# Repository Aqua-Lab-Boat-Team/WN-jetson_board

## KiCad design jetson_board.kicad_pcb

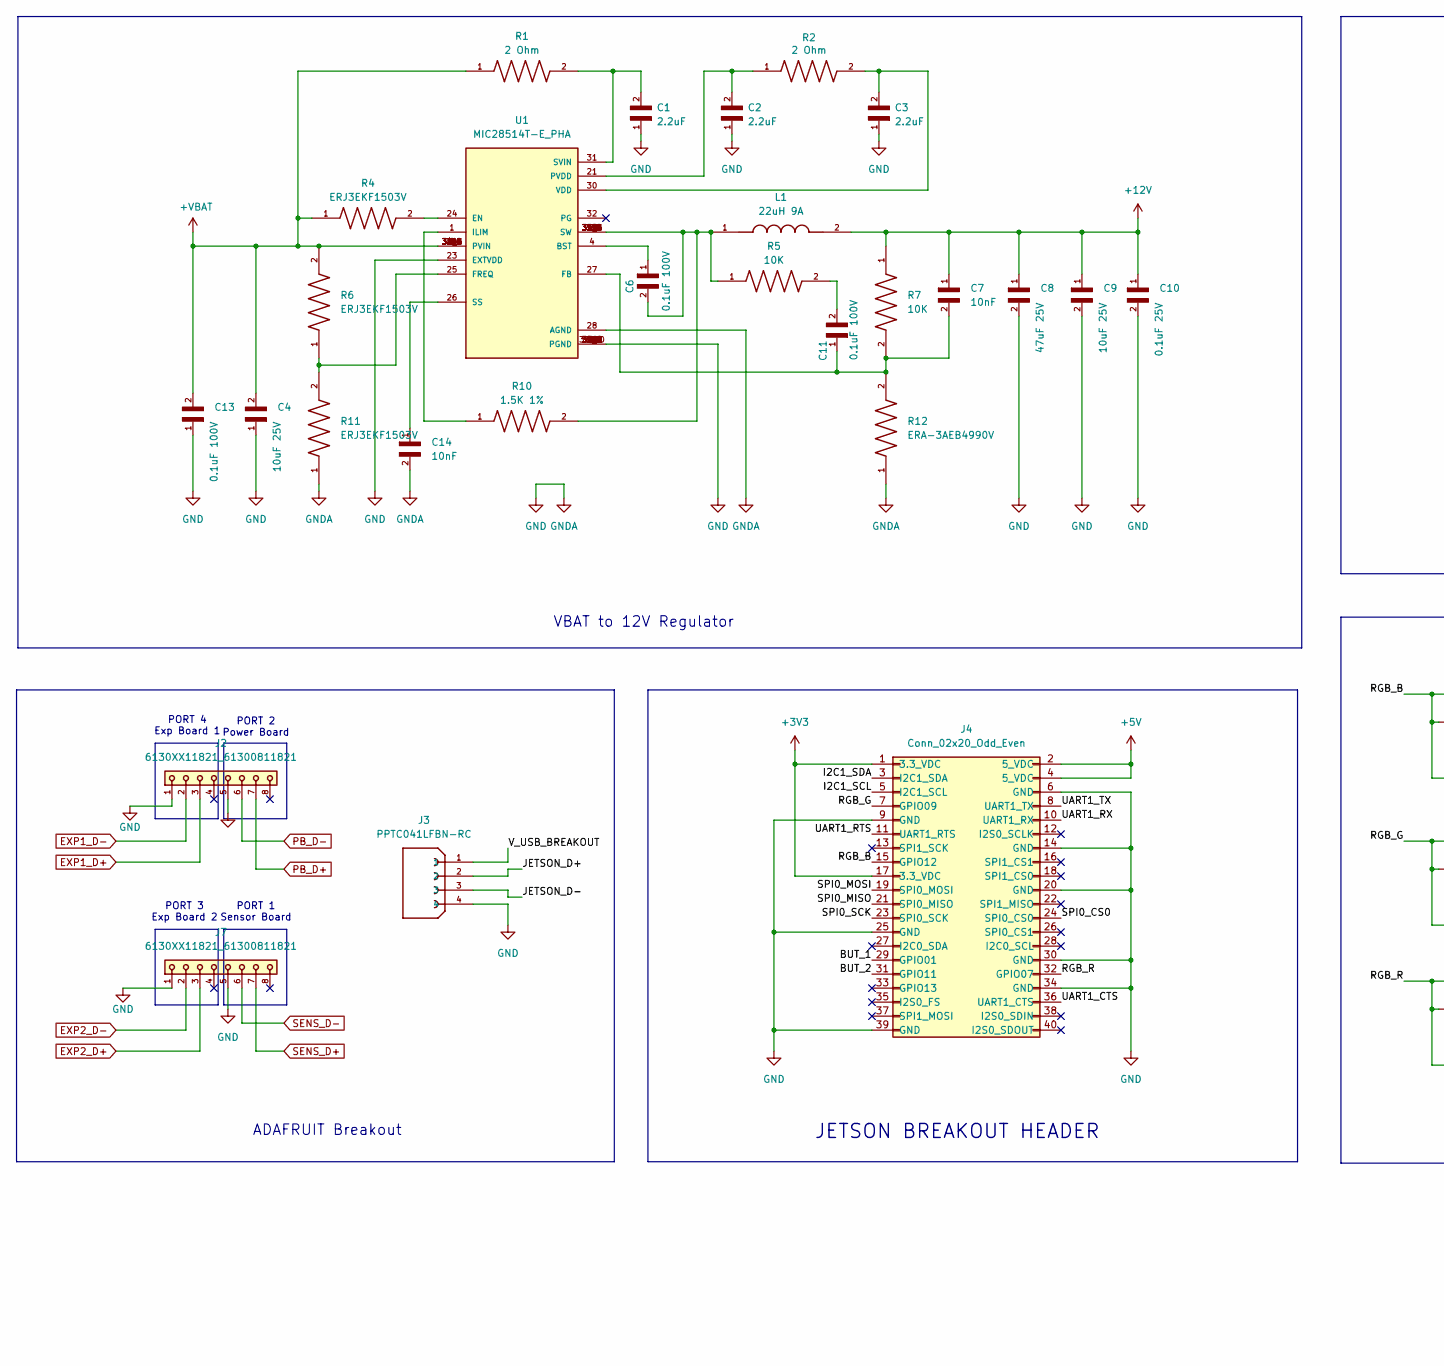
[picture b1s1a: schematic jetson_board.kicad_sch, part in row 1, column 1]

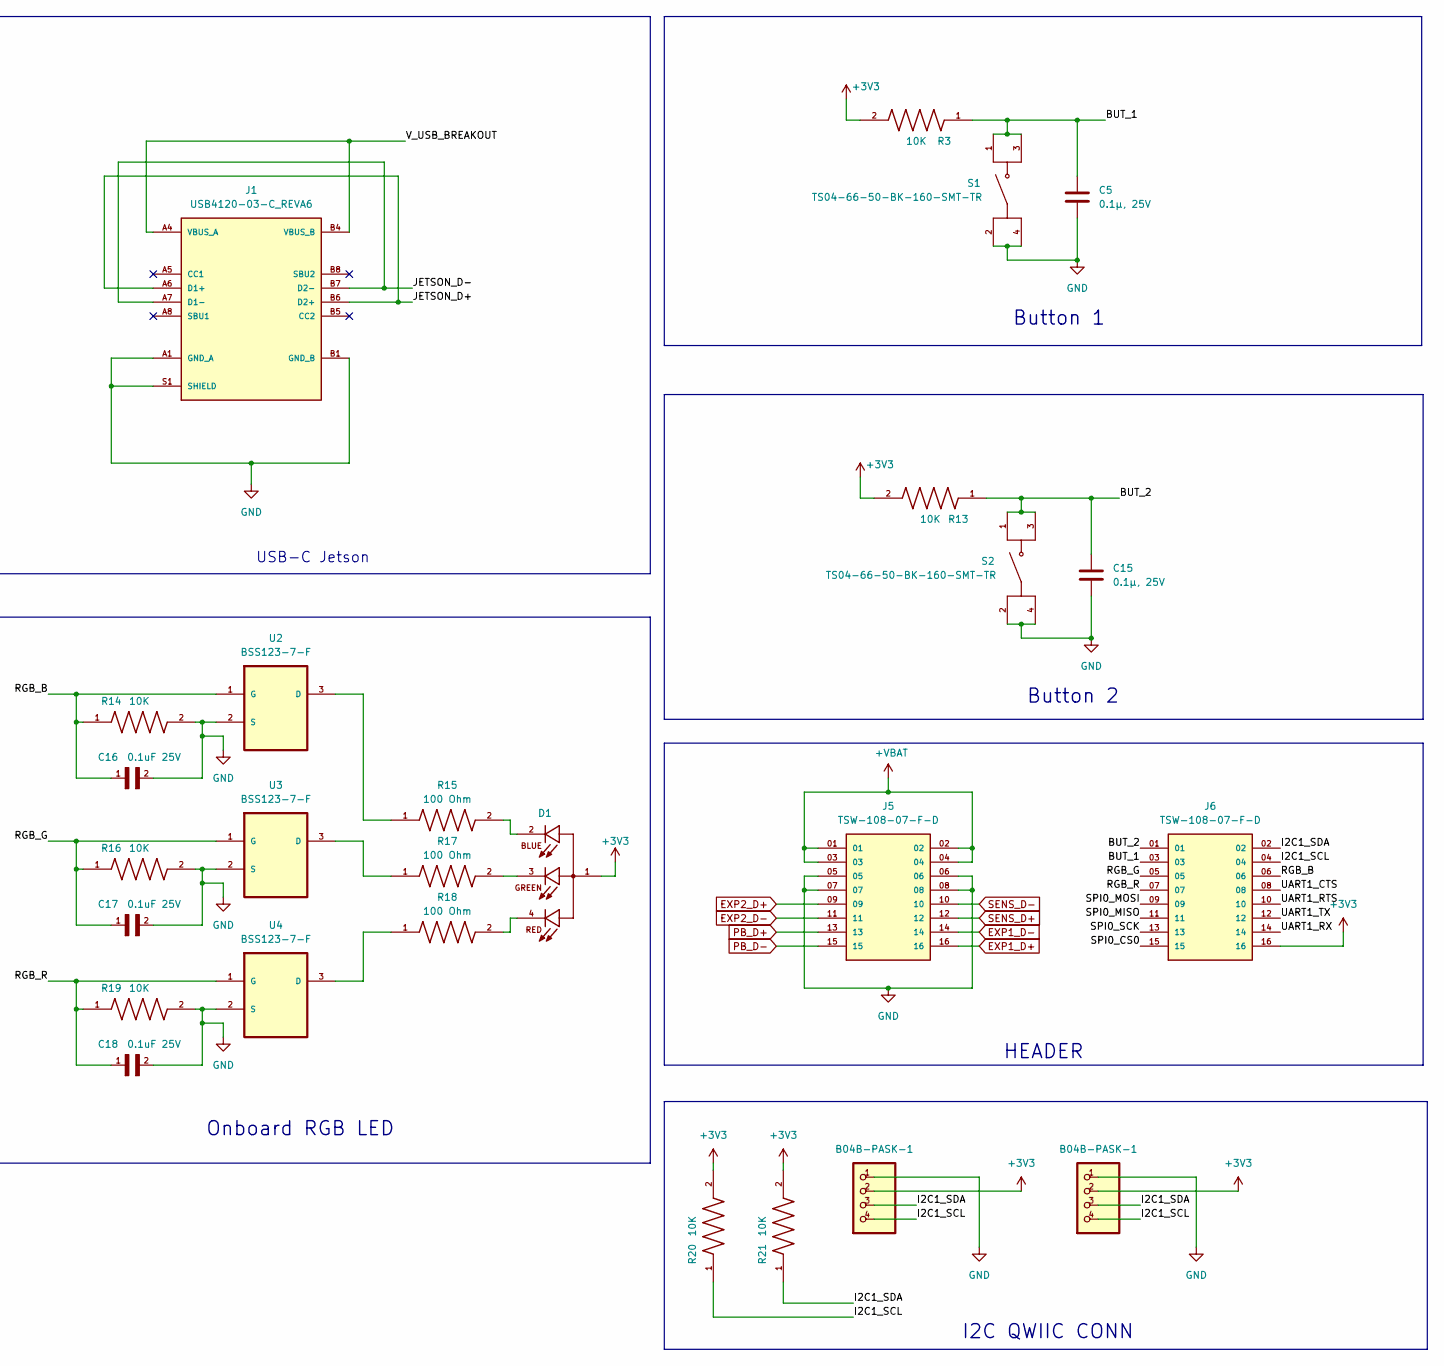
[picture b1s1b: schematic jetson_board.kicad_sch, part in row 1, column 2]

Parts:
C1, C2, C3: 2.2uF; CAPC1608X100N
C4, C9: 10uF 25V; CAPC2012X145N
C5, C15: 0.1µ, 25V; CAPC2012X95N
C6, C11, C13: 0.1uF 100V; CAPC2012X135N
C7, C14: 10nF; CAPC1608X90N
C8: 47uF 25V; CAPC3216X180N
C10, C16, C17, C18: 0.1uF 25V; CAPC2012X95N
D1: CLMVC-FKA-CL1D1L71BB7C3C3; LED_CLMVC-FKA-CL1D1L71BB7C3C3; PARTREV 14
J1: USB4120-03-C_REVA6; GCT_USB4120-03-C_REVA6; PARTREV A6
J2, J7: 6130XX11821_61300811821; 61300811821
J3: PPTC041LFBN-RC; SULLINS_PPTC041LFBN-RC; PARTREV J - 04/15/2015
J4: Conn_02x20_Odd_Even; 61234020621
J5, J6: TSW-108-07-F-D; SAMTEC_TSW-108-07-F-D; PARTREV R
JP1, JP2: B04B-PASK-1
L1: 22uH 9A; IND_SRP1265A-220M; PARTREV 04/20
R1, R2: 2 Ohm; RESC2012X65N
R3, R5, R7, R13, R14, R16, R19, R20, R21: 10K; RES_ERJ3EKF1001V; PARTREV 3/1/2020
R4, R6, R11: ERJ3EKF1503V; RES_ERJ3EKF1001V; PARTREV 3/1/2020
R10: 1.5K 1%; RES_ERJ3EKF1501V; PARTREV 3/1/2020
R12: ERA-3AEB4990V; RESC1608X55N
R15, R17, R18: 100 Ohm; RES_ERJ3EKF1000V; PARTREV 3/1/2020
S1, S2: TS04-66-50-BK-160-SMT-TR; SW_TS04-66-50-BK-160-SMT-TR; PARTREV 1.04mm
U1: MIC28514T-E_PHA; CONV_MIC28514T-E_PHA; PARTREV E
U2, U3, U4: BSS123-7-F; SOT95P240X110-3N; MPN BSS123-7-F

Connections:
+3V3: D1.1, J4.1 (3.3_VDC), J4.17 (3.3_VDC), J6.16, JP1.2, JP2.2, R3.2, R13.2, R20.2, R21.2
+5V: J4.2 (5_VDC), J4.4 (5_VDC)
+12V: C7.1, C8.1, C9.1, C10.1, L1.2, R7.1
+VBAT: C4.2, C13.2, J5.01, J5.02, J5.03, J5.04, R1.1, R4.1, R6.2, U1.5 (PVIN), U1.6 (PVIN), U1.7 (PVIN), U1.8 (PVIN), U1.9 (PVIN), U1.10 (PVIN), U1.11 (PVIN), U1.34 (PVIN), U1.34_1 (PVIN), U1.34_2 (PVIN), U1.34_3 (PVIN), U1.34_4 (PVIN), U1.34_5 (PVIN), U1.34_6 (PVIN)
/BUT_1: C5.1, J4.29 (GPIO01), J6.03, R3.1, S1.1, S1.3
/BUT_2: C15.1, J4.31 (GPIO11), J6.01, R13.1, S2.1, S2.3
/I2C1_SCL: J4.5 (I2C1_SCL), J6.04, JP1.4, JP2.4, R20.1
/I2C1_SDA: J4.3 (I2C1_SDA), J6.02, JP1.3, JP2.3, R21.1
/JETSON_D+: J1.A6 (D1+), J1.B6 (D2+), J3.2
/JETSON_D-: J1.A7 (D1-), J1.B7 (D2-), J3.3
/RGB_B: C16.1, J4.15 (GPIO12), J6.06, R14.1, U2.1 (G)
/RGB_G: C17.1, J4.7 (GPIO09), J6.05, R16.1, U3.1 (G)
/RGB_R: C18.1, J4.32 (GPIO07), J6.07, R19.1, U4.1 (G)
/SPI0_CS0: J4.24 (SPI0_CS0), J6.15
/SPI0_MISO: J4.21 (SPI0_MISO), J6.11
/SPI0_MOSI: J4.19 (SPI0_MOSI), J6.09
/SPI0_SCK: J4.23 (SPI0_SCK), J6.13
/UART1_CTS: J4.36 (UART1_CTS), J6.08
/UART1_RTS: J4.11 (UART1_RTS), J6.10
/UART1_RX: J4.10 (UART1_RX), J6.14
/UART1_TX: J4.8 (UART1_TX), J6.12
/V_USB_BREAKOUT: J1.A4 (VBUS_A), J1.A9 (VBUS_A), J1.B4 (VBUS_B), J1.B9 (VBUS_B), J3.1
EXP1_D+: J2.3, J5.16
EXP1_D-: J2.2, J5.14
EXP2_D+: J5.09, J7.3
EXP2_D-: J5.11, J7.2
GND: C1.1, C2.1, C3.1, C4.1, C5.2, C8.2, C9.2, C10.2, C13.1, C14.2, C15.2, C16.2, C17.2, C18.2, J1.A1 (GND_A), J1.A12 (GND_A), J1.B1 (GND_B), J1.B12 (GND_B), J1.S1 (SHIELD), J1.S2 (SHIELD), J1.S3 (SHIELD), J1.S4 (SHIELD), J2.1, J2.5, J3.4, J4.6 (GND), J4.9 (GND), J4.14 (GND), J4.20 (GND), J4.25 (GND), J4.30 (GND), J4.34 (GND), J4.39 (GND), J5.05, J5.06, J5.07, J5.08, J7.1, J7.5, JP1.1, JP2.1, R11.1, R12.1, R14.2, R16.2, R19.2, S1.2, S1.4, S2.2, S2.4, U1.2 (PGND), U1.16 (PGND), U1.17 (PGND), U1.18 (PGND), U1.19 (PGND), U1.22 (PGND), U1.23 (EXTVDD), U1.28 (AGND), U1.29 (PGND), U1.33 (PGND), U1.33_1 (PGND), U1.33_2 (PGND), U1.33_3 (PGND), U1.33_4 (PGND), U1.33_5 (PGND), U1.33_6 (PGND), U1.33_7 (PGND), U1.33_8 (PGND), U1.33_9 (PGND), U1.33_10 (PGND), U1.36 (PGND), U1.36_1 (PGND), U1.36_2 (PGND), U2.2 (S), U3.2 (S), U4.2 (S)
unnamed: C6.2, L1.1, R5.1, R10.2, U1.3 (SW), U1.12 (SW), U1.13 (SW), U1.14 (SW), U1.15 (SW), U1.20 (SW), U1.35 (SW), U1.35_1 (SW), U1.35_2 (SW), U1.35_3 (SW), U1.35_4 (SW), U1.35_5 (SW), U1.35_6 (SW)
unnamed: C11.2, R5.2
unnamed: D1.2, R15.2
unnamed: D1.3, R17.2
unnamed: D1.4, R18.2
unnamed: C6.1, U1.4 (BST)
unnamed: R4.2, U1.24 (EN)
unnamed: C7.2, C11.1, R7.2, R12.2, U1.27 (FB)
unnamed: R6.1, R11.2, U1.25 (FREQ)
unnamed: R10.1, U1.1 (ILIM)
unnamed: C2.2, R2.1, U1.21 (PVDD)
unnamed: C14.1, U1.26 (SS)
unnamed: C1.2, R1.2, U1.31 (SVIN)
unnamed: C3.2, R2.2, U1.30 (VDD)
unnamed: R15.1, U2.3 (D)
unnamed: R17.1, U3.3 (D)
unnamed: R18.1, U4.3 (D)
PB_D+: J2.7, J5.13
PB_D-: J2.6, J5.15
SENS_D+: J5.12, J7.7
SENS_D-: J5.10, J7.6

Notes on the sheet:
Onboard RGB LED
Button 1
PORT 1 Sensor Board
Button 2
JETSON BREAKOUT HEADER
PORT 4 Exp Board 1
PORT 2 Power Board
PORT 3 Exp Board 2
HEADER
I2C QWIIC CONN
VBAT to 12V Regulator
ADAFRUIT Breakout
USB-C Jetson

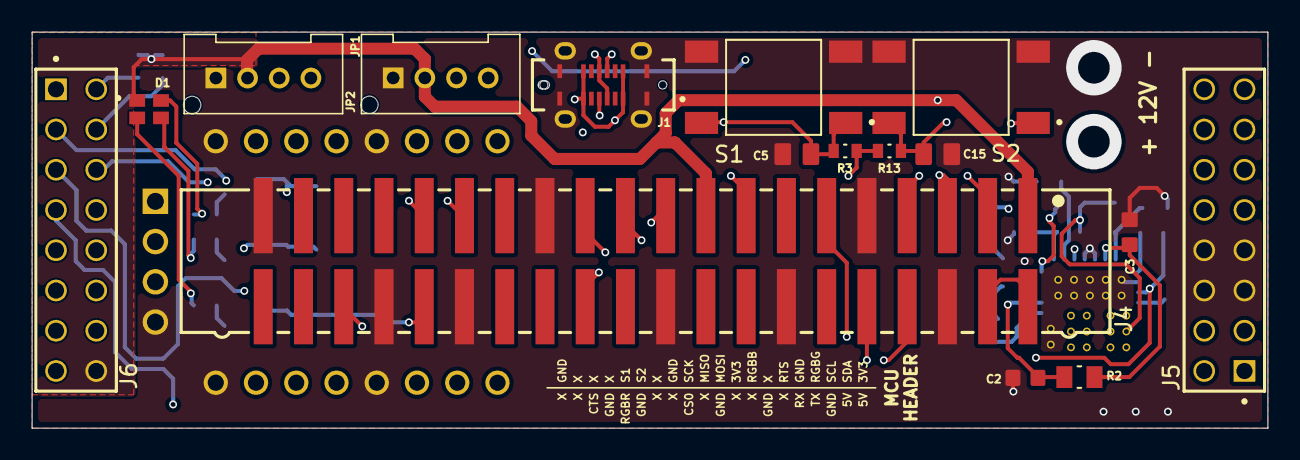
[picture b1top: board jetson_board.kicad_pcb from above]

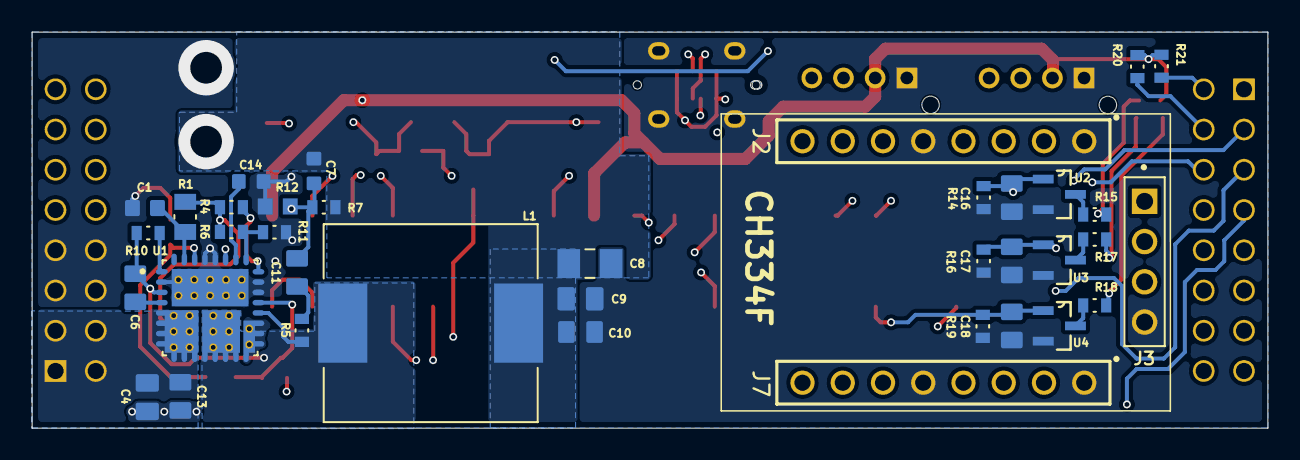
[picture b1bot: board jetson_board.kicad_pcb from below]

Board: 4 copper layers, 78.0 x 25.0 mm, 53 parts (37 on the bottom side), 48 nets.
